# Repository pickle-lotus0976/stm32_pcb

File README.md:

# STM32 PCB Design

## Overview

This is my first PCB design project. It is essentially a clone of the board designed by Philip Salmony, that was featured in his YouTube video tutorial: [KiCad STM32 PCB Design Full Tutorial - Phil's Lab #65](https://youtu.be/aVUqaB0IMh4?si=W57RVr_CsgqvWgg2). I have not experimented with the design yet, since I am just getting started, but I will definitely add more features in the future using this design as tha starting point. I am incredibly thankful to him for the tutorial. The design contains an **STM32F103C8T6 microcontroller** and an **AMS1117-3.3 linear power regulator**. It has three communication-protocol connectorsnamely USART, I²C & Serial Wire Debugging (SWD). The pinout was created by Philip using STM32CubeIDE. The only part of the tutorial I did not follow was the placement and routing. I completed those myself so that I could learn from my mistakes.

## Schematic

## PCB Layout

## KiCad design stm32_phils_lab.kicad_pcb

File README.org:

* STM32 PCB Design
** Overview
This is my first PCB design project. It is basically a clone of the board designed by Philip Salmony, part of his YouTube video tutorial [[https://youtu.be/aVUqaB0IMh4?si=W57RVr_CsgqvWgg2][KiCAD STM32 PCB Design Full Tutorial - Phil's Lab #65]]. I haven't experimented with the design yet, since I am just getting started but I will definitely add some features in the future. I am incredibly thankful to him. The design contains a STM32F103C8T6 microcotroller and a AMS1117-3.3 linar power regulator, it has three communication protocol male connectors namely USART & I2C along with Serial Wire Debuging. The pinout was done by Philip using STM32Cube IDE. The only thing that I didn't follow from the tutorial was the placment and routing, I did it by myself so that I could learn from my mistakes.
** Schematic
[[/home/noah/Documents/project/stsm32_pcb/schematic.png]]
** PCB Layout
[[/home/noah/Documents/project/stsm32_pcb/layout.png]]

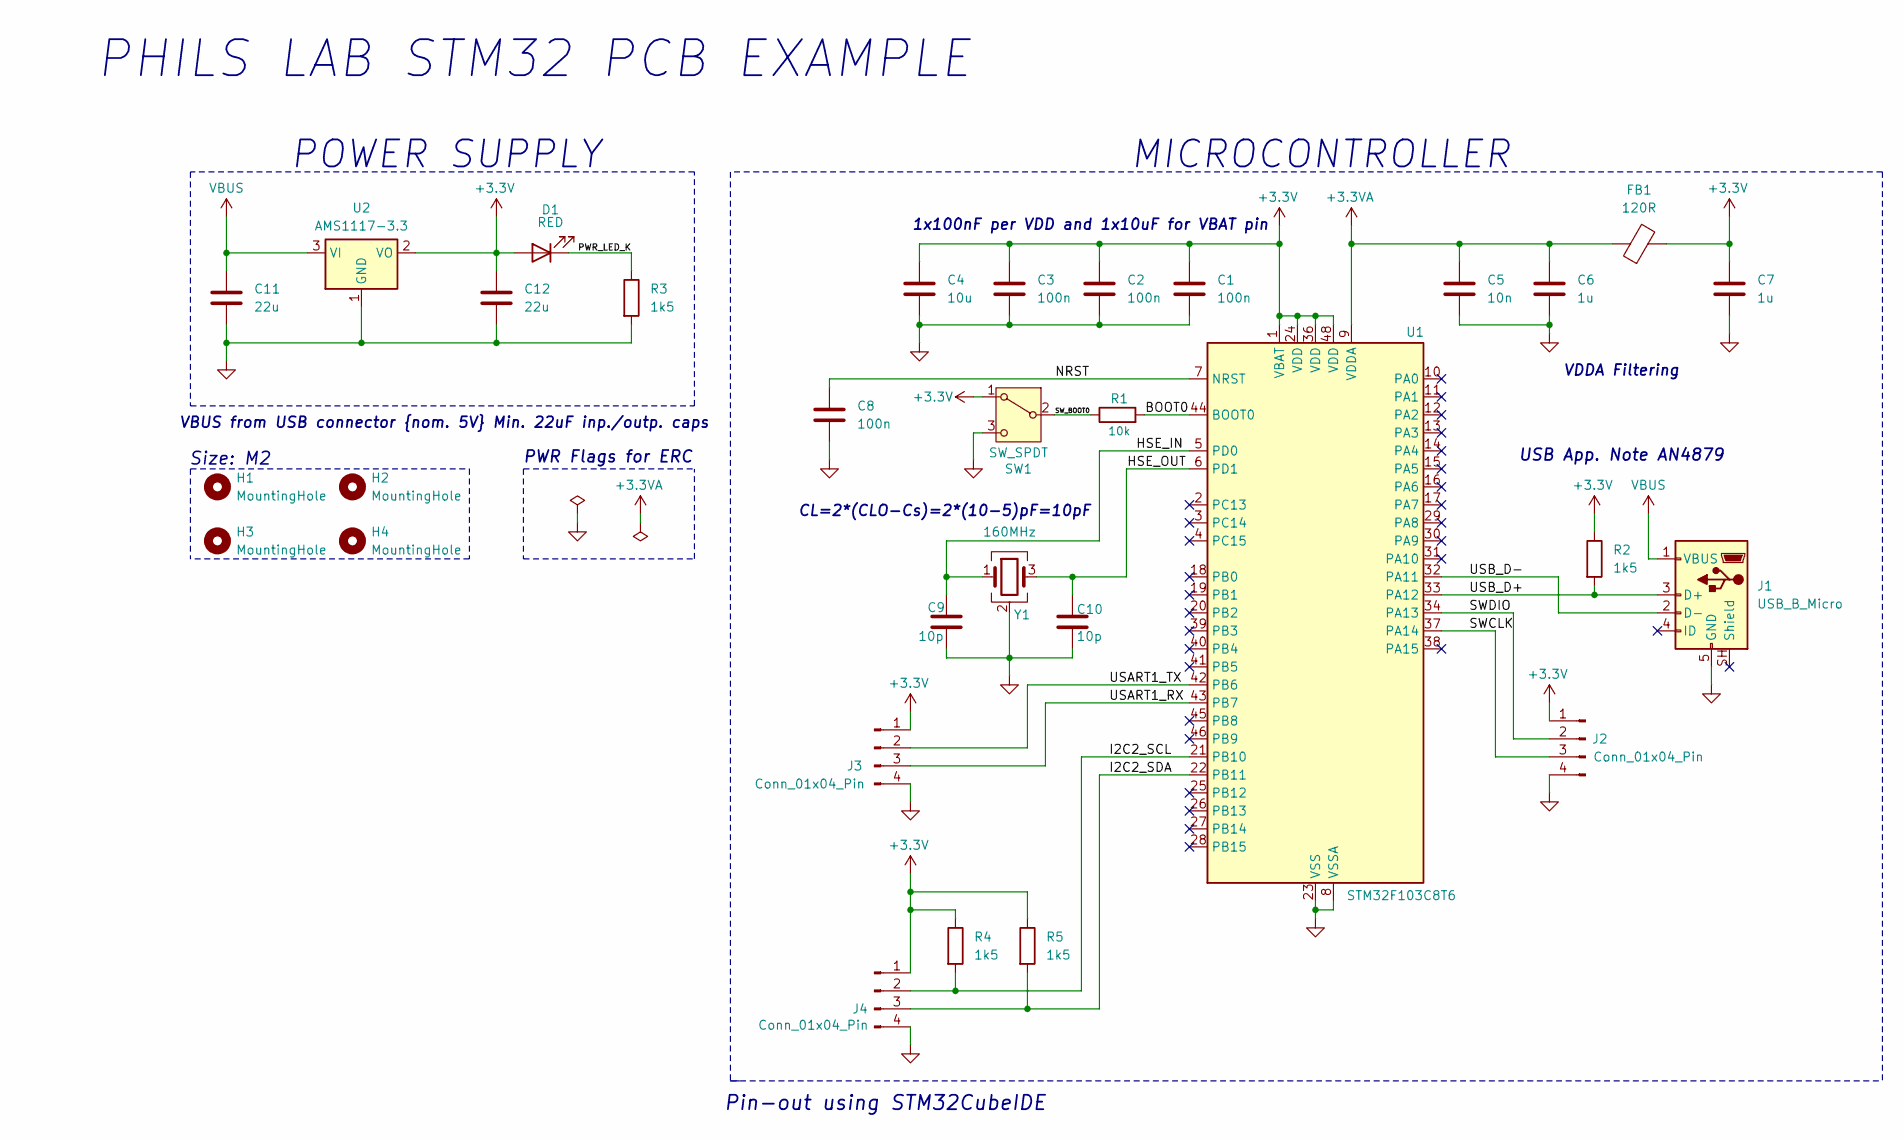
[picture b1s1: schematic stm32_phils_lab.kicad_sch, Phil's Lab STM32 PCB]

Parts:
C1, C2, C3, C8: 100n; C_0402_1005Metric
C4: 10u; C_0603_1608Metric
C5: 10n; C_0402_1005Metric
C6, C7: 1u; C_0402_1005Metric
C9, C10: 10p; C_0402_1005Metric
C11, C12: 22u; C_0805_2012Metric
D1: RED; LED_0603_1608Metric
FB1: 120R; L_0603_1608Metric
H1, H2, H3, H4: MountingHole; MountingHole_2.2mm_M2
J1: USB_B_Micro; USB_Micro-B_Wuerth_629105150521
J2, J3, J4: Conn_01x04_Pin; PinHeader_1x04_P2.54mm_Vertical
R1: 10k; R_0402_1005Metric
R2, R3, R4, R5: 1k5; R_0402_1005Metric
SW1: SW_SPDT; SW_SPDT_PCM12
U1: STM32F103C8T6; LQFP-48_7x7mm_P0.5mm
U2: AMS1117-3.3; SOT-223-3_TabPin2
Y1: 160MHz; Crystal_SMD_3225-4Pin_3.2x2.5mm

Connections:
+3.3V: C1.1, C2.1, C3.1, C4.1, C7.1, C12.1, D1.2 (A), FB1.2, J2.1, J3.1, J4.1, R2.1, R4.1, R5.1, SW1.1 (A), U1.1 (VBAT), U1.24 (VDD), U1.36 (VDD), U1.48 (VDD), U2.2 (VO)
+3.3VA: C5.1, C6.1, FB1.1, U1.9 (VDDA)
/BOOT0: R1.2, U1.44 (BOOT0)
/HSE_IN: C9.1, U1.5 (PD0), Y1.1
/HSE_OUT: C10.1, U1.6 (PD1), Y1.3
/I2C2_SCL: J4.2, R4.2, U1.21 (PB10)
/I2C2_SDA: J4.3, R5.2, U1.22 (PB11)
/NRST: C8.1, U1.7 (NRST)
/PWR_LED_K: D1.1 (K), R3.1
/SWCLK: J2.3, U1.37 (PA14)
/SWDIO: J2.2, U1.34 (PA13)
/SW_BOOT0: R1.1, SW1.2 (B)
/USART1_RX: J3.3, U1.43 (PB7)
/USART1_TX: J3.2, U1.42 (PB6)
/USB_D+: J1.3 (D+), R2.2, U1.33 (PA12)
/USB_D-: J1.2 (D-), U1.32 (PA11)
GND: C1.2, C2.2, C3.2, C4.2, C5.2, C6.2, C7.2, C8.2, C9.2, C10.2, C11.2, C12.2, J1.5 (GND), J2.4, J3.4, J4.4, R3.2, SW1.3 (C), U1.8 (VSSA), U1.23 (VSS), U1.35 (VSS), U1.47 (VSS), U2.1 (GND), Y1.2 (G), Y1.4 (G)
VBUS: C11.1, J1.1 (VBUS), U2.3 (VI)

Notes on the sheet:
POWER SUPPLY
USB App. Note AN4879
PHILS LAB STM32 PCB EXAMPLE
Size: M2
VDDA Filtering
Pin-out using STM32CubeIDE
PWR Flags for ERC
VBUS from USB connector {nom. 5V} Min. 22uF inp./outp. caps
CL=2*(CLO-Cs)=2*(10-5)pF=10pF
MICROCONTROLLER
1x100nF per VDD and 1x10uF for VBAT pin

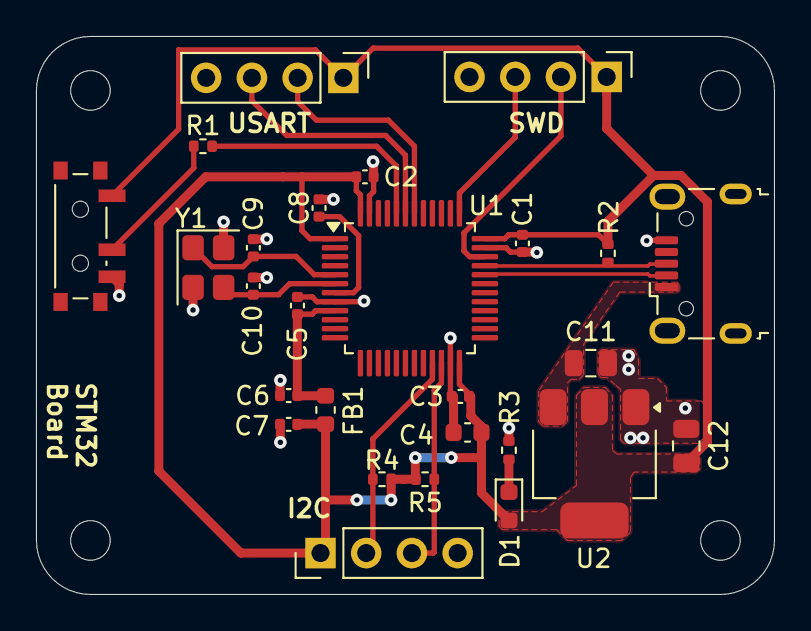
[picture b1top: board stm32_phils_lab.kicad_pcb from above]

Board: 2 copper layers, 41.0 x 31.0 mm, 31 parts (0 on the bottom side), 18 nets.
